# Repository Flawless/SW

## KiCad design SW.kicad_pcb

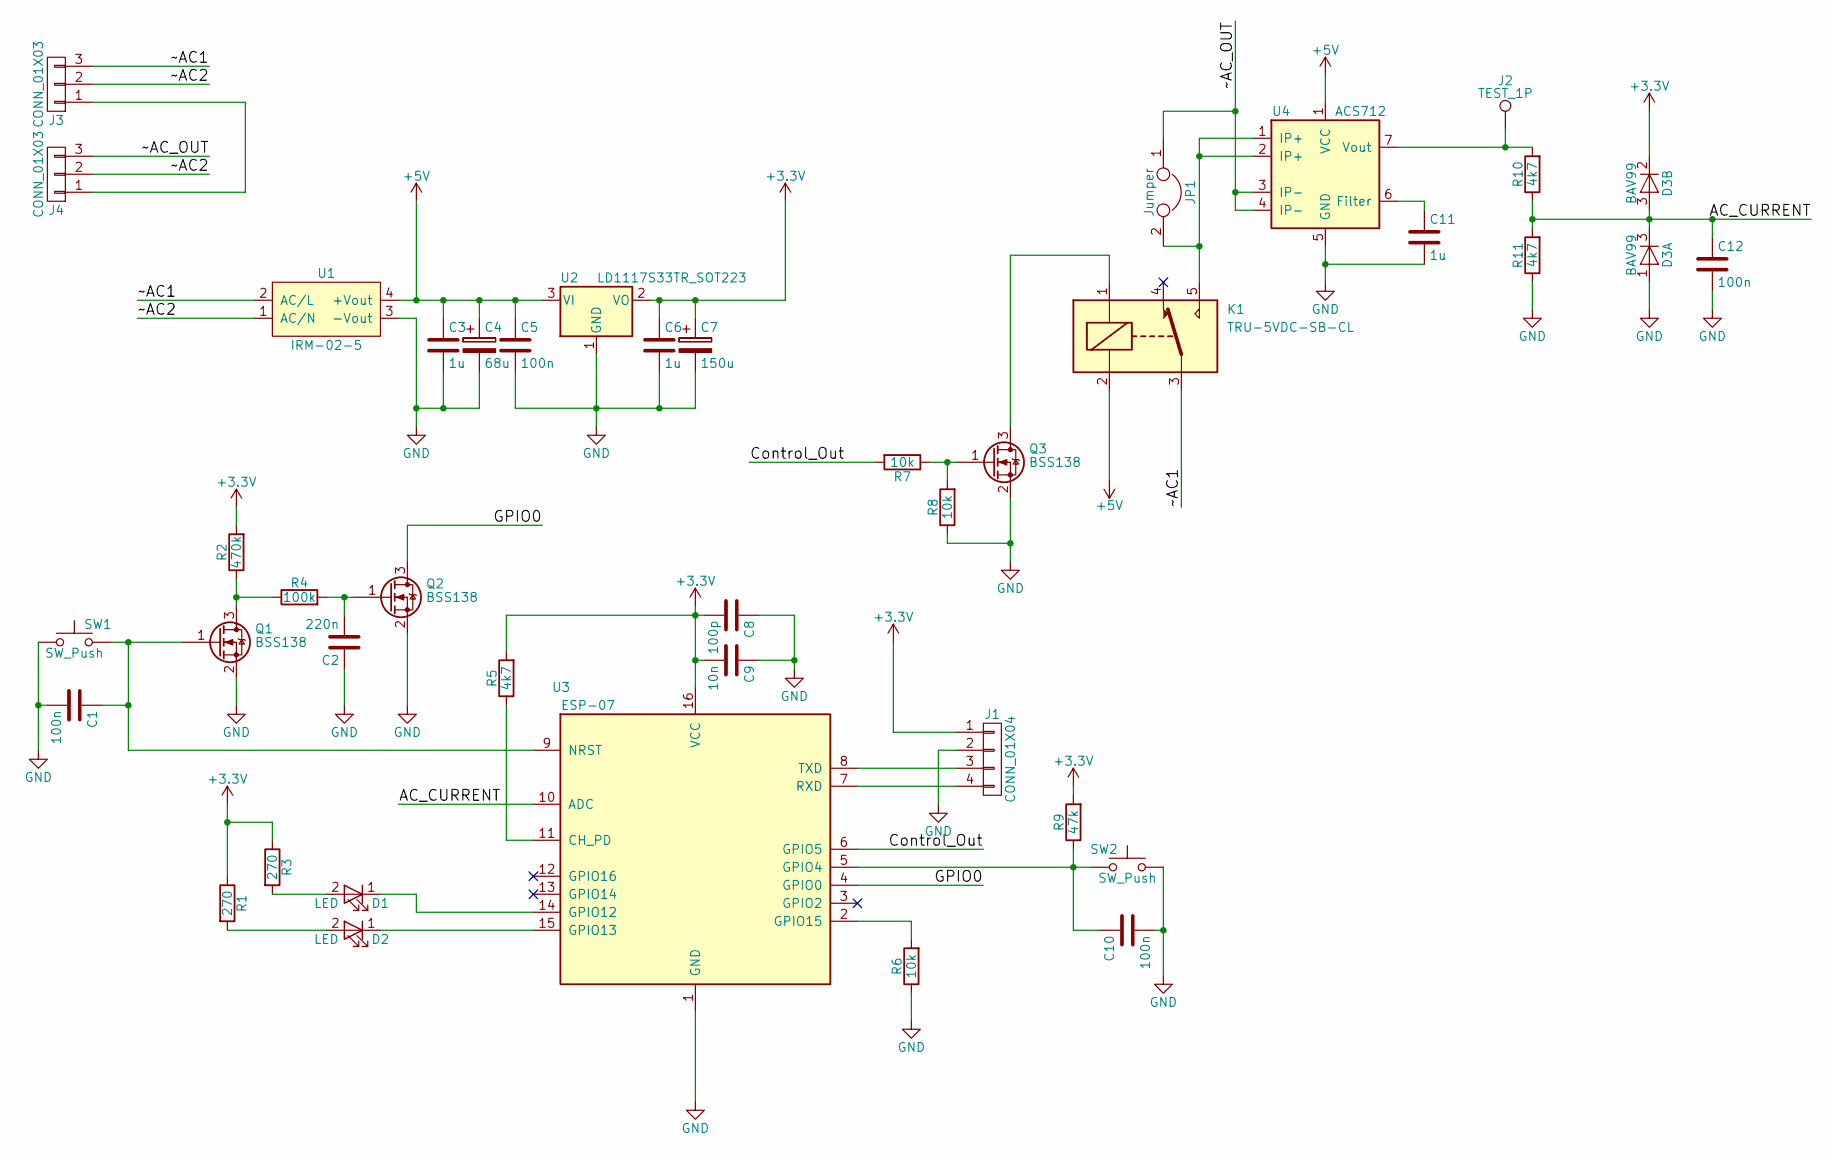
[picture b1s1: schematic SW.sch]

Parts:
C1, C5, C10, C12: 100n; C_0603_HandSoldering
C2: 220n; C_0603_HandSoldering
C3, C6, C11: 1u; C_0603_HandSoldering
C4: 68u; CP_Tantalum_Case-D_EIA-7343-31_Hand; Voltage 6.3V
C7: 150u; CP_Tantalum_Case-D_EIA-7343-31_Hand; Voltage 4V
C8: 100p; C_0603_HandSoldering
C9: 10n; C_0603_HandSoldering
D1, D2: LED; LED_0603
D3: BAV99; SOT-23
J1: CONN_01X04; Molex_PicoBlade_53047-0410_04x1.25mm_Straight
J2: TEST_1P; Measurement_Point_Round-SMD-Pad_Small
J3, J4: CONN_01X03; AK300-3
JP1: Jumper; GS2
K1: TRU-5VDC-SB-CL; TRU-Relay
Q1, Q2, Q3: BSS138; SOT-23
R1, R3: 270; R_0603_HandSoldering
R2: 470k; R_0603_HandSoldering
R4: 100k; R_0603_HandSoldering
R5, R10, R11: 4k7; R_0603_HandSoldering
R6, R7, R8: 10k; R_0603_HandSoldering
R9: 47k; R_0603_HandSoldering
SW1, SW2: SW_Push; DTSGL-61K
U1: IRM-02-5; ACDC-Converter_MeanWell-IRM-02-x
U2: LD1117S33TR_SOT223; SOT-223-3Lead_TabPin2
U3: ESP-07
U4: ACS712; SOIC-8

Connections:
+3V3: C6.1, C7.1, C8.2, C9.2, D3.2 (K), J1.1, R1.1, R2.2, R3.1, R5.2, R9.2, U2.2 (VO), U3.16 (VCC)
/AC_CURRENT: C12.1, D3.3 (K), R10.1, R11.2, U3.10 (ADC)
/Control_Out: R7.2, U3.6 (GPIO5)
/GPIO0: Q2.3 (D), U3.4 (GPIO0)
/~~AC1: J3.3, K1.3, U1.2 (AC/L)
/~~AC2: J3.2, J4.2, U1.1 (AC/N)
/~~AC_OUT: J4.3, JP1.1, U4.3 (IP-), U4.4 (IP-)
GND: C1.2, C2.1, C3.2, C4.2, C5.2, C6.2, C7.2, C8.1, C9.1, C10.2, C11.2, C12.2, D3.1 (A), J1.2, Q1.2 (S), Q2.2 (S), Q3.2 (S), R6.1, R8.1, R11.1, SW1.1, SW2.1, U1.3 (-Vout), U2.1 (GND), U3.1 (GND), U4.5 (GND)
unnamed: C1.1, Q1.1 (G), SW1.2, U3.9 (NRST)
unnamed: C2.2, Q2.1 (G), R4.2
unnamed: C10.1, R9.1, SW2.2, U3.5 (GPIO4)
unnamed: C11.1, U4.6 (Filter)
unnamed: D1.1 (K), U3.14 (GPIO12)
unnamed: D1.2 (A), R3.2
unnamed: D2.1 (K), U3.15 (GPIO13)
unnamed: D2.2 (A), R1.2
unnamed: J1.3, U3.8 (TXD)
unnamed: J1.4, U3.7 (RXD)
unnamed: J2.1, R10.2, U4.7 (Vout)
unnamed: J3.1, J4.1
unnamed: K1.1, Q3.3 (D)
unnamed: Q1.3 (D), R2.1, R4.1
unnamed: Q3.1 (G), R7.1, R8.2
unnamed: R5.1, U3.11 (CH_PD)
unnamed: R6.2, U3.2 (GPIO15)

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
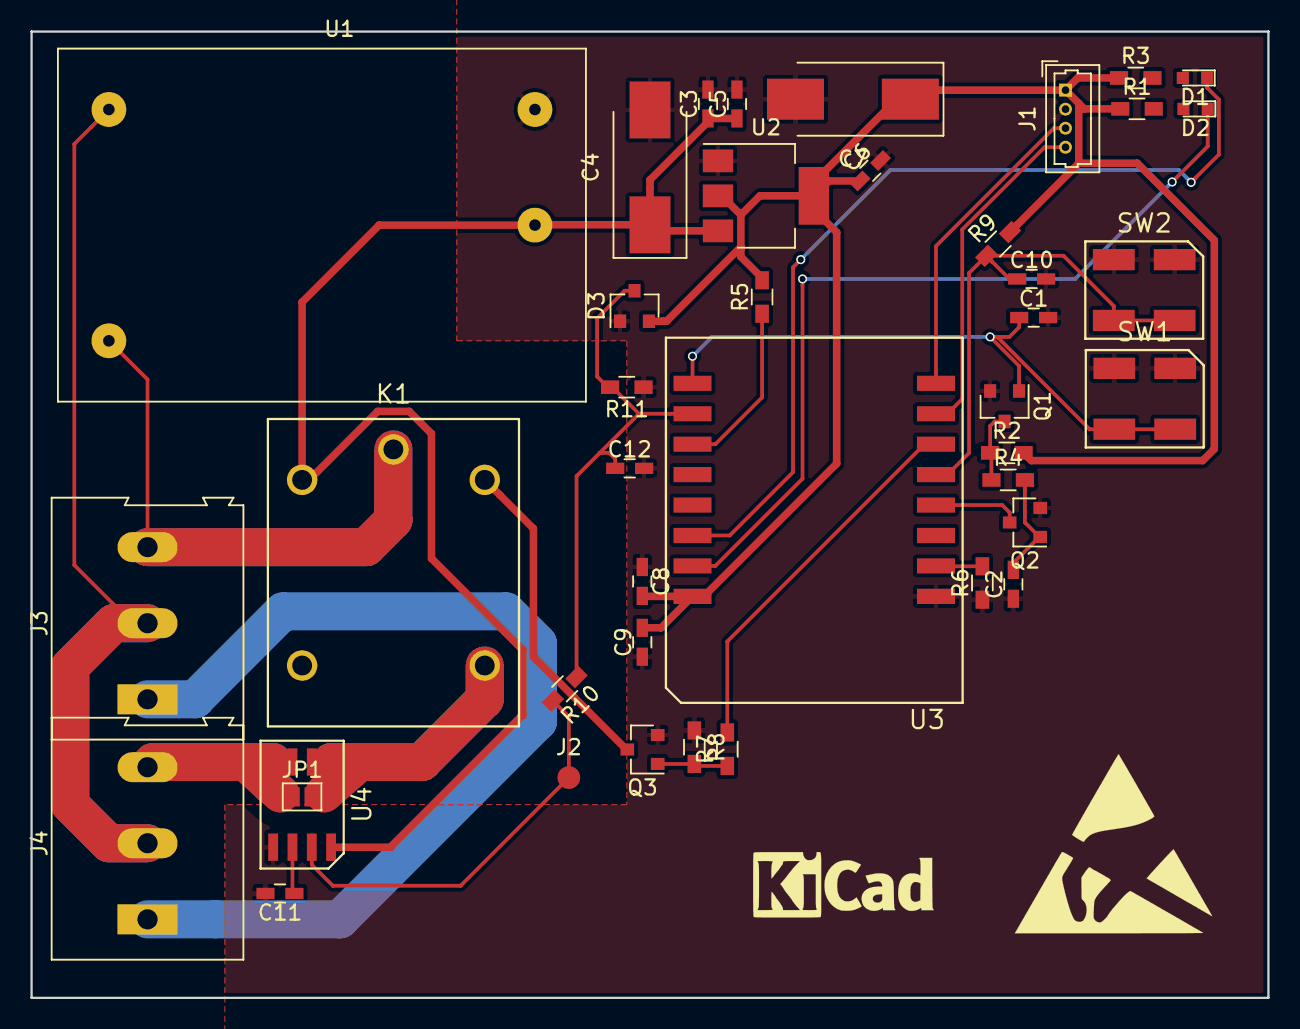
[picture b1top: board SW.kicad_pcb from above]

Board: 2 copper layers, 81.3 x 63.5 mm, 41 parts (0 on the bottom side), 27 nets.
